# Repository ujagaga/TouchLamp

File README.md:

# TouchLamp

This is the PCB and Firmware for an LED lamp acivated by a touch on the sensor. 

The firmware is written using Eclipse and AVR toolchain. I used AtTiny2313, but you can use any Atmel MCU with at least 1KB of flash.

The sensor can be a piece of metal (preferably isolated with paint) size of a couple of sqare centimeters. The size is not critical. 
I have used a piece of copper 1x1cm and also 3x3cm. The firmware automatically calibrates at startup.

When you hold your finger on the sensor, the light intensity increases. If you touch it shortly, the light toggles on/off.
The preset light intensity is saved in the EEPROM so it does not get forgotten through power failures.

The touch is detected through changes in the capacity by measuring the time it takes to charge the capacitor, so you should not use long wires to connect the sensor.
Using a coaxial cable would increase minimum capacity and decrease change in capacity. Sensitivity can be adjusted by changing the "DETECT_COEF".
The length of the sensor wire should not exceed 10cm. There is also a fixed capacity which is used as a reference because the threashold of logic levels changes
as the controller operates.

I used F_CPU 8MHz, but it should work with any other frequency. If you use smaller frequency, you get less resolution and less sensitivity.
I used prototype PCB with dots at 2,54mm and did my best to minimize the PCB size. The transistor is in SMD package, but you could use any other transistor in any other package.

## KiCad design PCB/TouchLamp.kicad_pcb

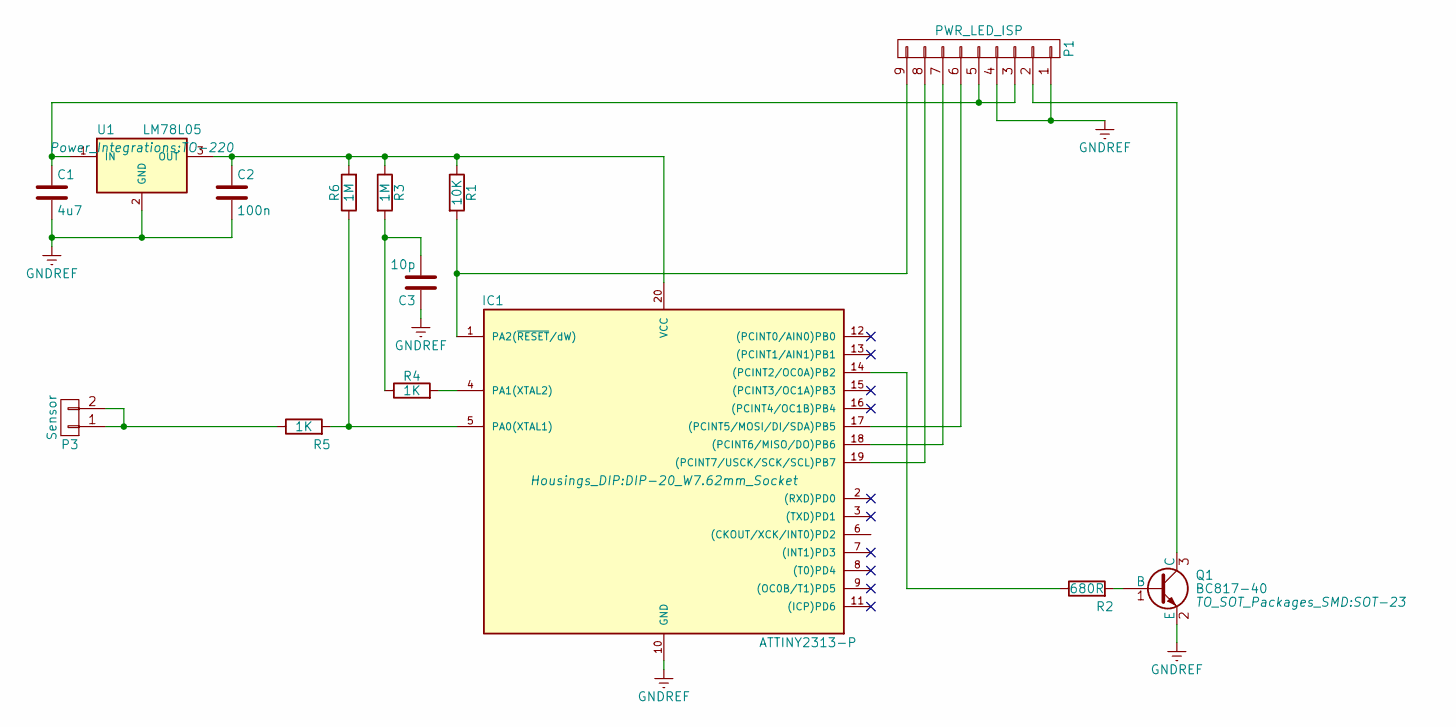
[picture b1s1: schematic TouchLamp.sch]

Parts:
C1: 4u7; C_0805_HandSoldering
C2: 100n; C_0805_HandSoldering
C3: 10p; C_0805_HandSoldering
IC1: ATTINY2313-P; DIP-20_W7.62mm_Socket
P1: PWR_LED_ISP; Socket_Strip_Angled_1x09_Pitch2.54mm
P3: Sensor; Socket_Strip_Angled_1x02_Pitch2.54mm
Q1: BC817-40; SOT-23
R1: 10K; R_0805_HandSoldering
R2: 680R; R_0805_HandSoldering
R3, R6: 1M; R_0805_HandSoldering
R4, R5: 1K; R_0805_HandSoldering
U1: LM78L05; TO-220

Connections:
GNDREF: C1.2, C2.2, C3.1, IC1.10 (GND), P1.1, P1.4, Q1.2 (E), U1.2 (GND)
unnamed: C1.1, P1.3, P1.5, U1.1 (IN)
unnamed: C2.1, IC1.20 (VCC), R1.1, R3.1, R6.2, U1.3 (OUT)
unnamed: C3.2, R3.2, R4.1
unnamed: IC1.1 (PA2(~RESET~/dW)), P1.9, R1.2
unnamed: IC1.4 (PA1(XTAL2)), R4.2
unnamed: IC1.5 (PA0(XTAL1)), R5.2, R6.1
unnamed: IC1.14 ((PCINT2/OC0A)PB2), R2.1
unnamed: IC1.17 ((PCINT5/MOSI/DI/SDA)PB5), P1.6
unnamed: IC1.18 ((PCINT6/MISO/DO)PB6), P1.7
unnamed: IC1.19 ((PCINT7/USCK/SCK/SCL)PB7), P1.8
unnamed: P1.2, Q1.3 (C)
unnamed: P3.1, P3.2, R5.1
unnamed: Q1.1 (B), R2.2

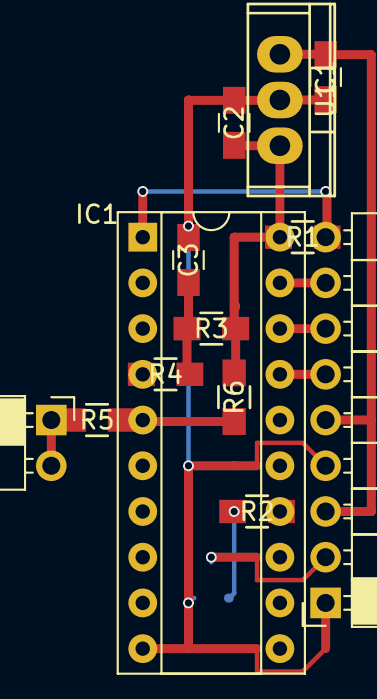
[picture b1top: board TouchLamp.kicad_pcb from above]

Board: 2 copper layers, 14 parts (1 on the bottom side), 14 nets.

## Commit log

2017-02-21 PCB, Schematic and FW
2017-02-21 optimized the PCB and adjusted the FW
2017-02-21 Optimized the fw some more
2017-02-21 Added low pass filter to sensor detection routine
